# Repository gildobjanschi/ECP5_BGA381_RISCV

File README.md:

# Blue Whale Hardware
ECP5 FPGA board for developing a RISCV processor.

## Software
The ECP5 FPGA board was developed to enable the development of a RISCV processor and allow for for an extension connector. See the [RISCV_PROCESSOR](https://github.com/gildobjanschi/RISCV_PROCESSOR) project for detailed explanation of the Verilog code developed for this board.

## Project Status
The HW has been fully verified as part of the [RISCV_PROCESSOR](https://github.com/gildobjanschi/RISCV_PROCESSOR) project. An [extension board](https://github.com/gildobjanschi/ECP5_BGA381_RISCV_EXT)  was developed to test the extension interface. 

## How To setup KiCAD
Checkout the KiCAD project and open it. In the Configure Paths dialog add: Name: ECP5_BGA381_RISCV and Path: "The full path to the GitHub directory"/GitHub/ECP5_BGA381_RISCV

In the Manage Symbol Libraries click the Project Specific Libraries tab and add: Name: ECP5_BGA381_RISCV and Library Path: ${ECP5_BGA381_RISCV}/symbols/Symbols.kicad_sym

In the Manage Footprint Libraries click the Project Specific Libraries tab and add: Name: ECP5_BGA381_RISCV and Library Path: ${ECP5_BGA381_RISCV}/footprints/Footprints.pretty

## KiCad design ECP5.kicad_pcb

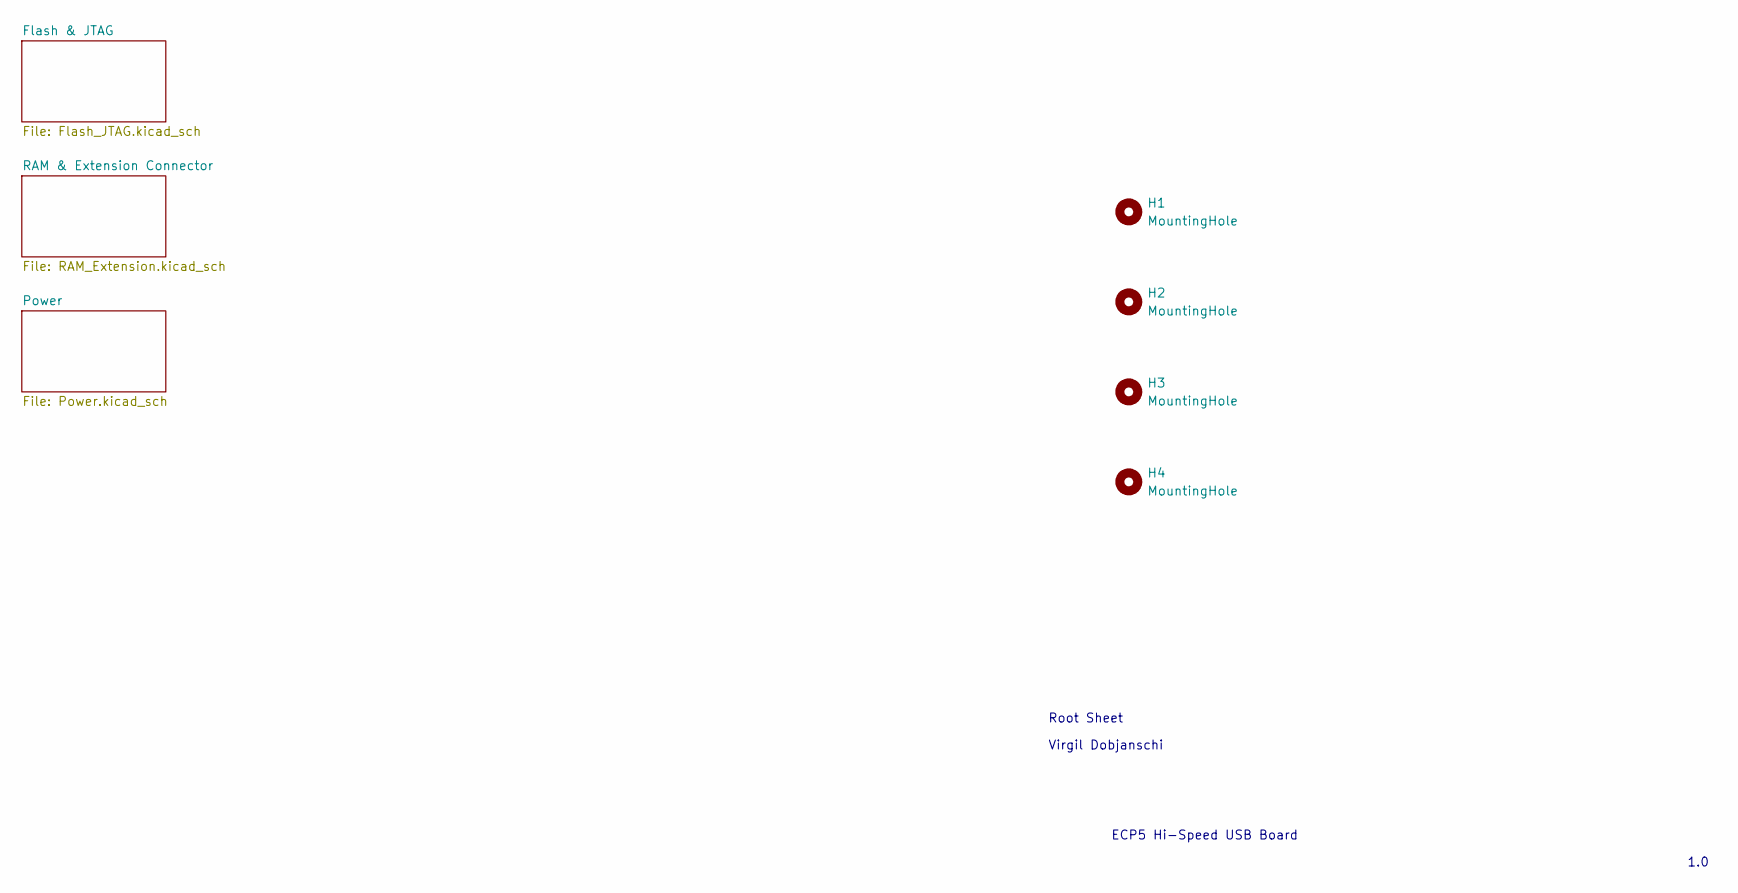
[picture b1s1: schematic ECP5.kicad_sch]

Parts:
H1, H2, H3, H4: MountingHole; MountingHole_3.2mm_M3

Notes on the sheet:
ECP5 Hi-Speed USB Board
Root Sheet
Virgil Dobjanschi
1.0

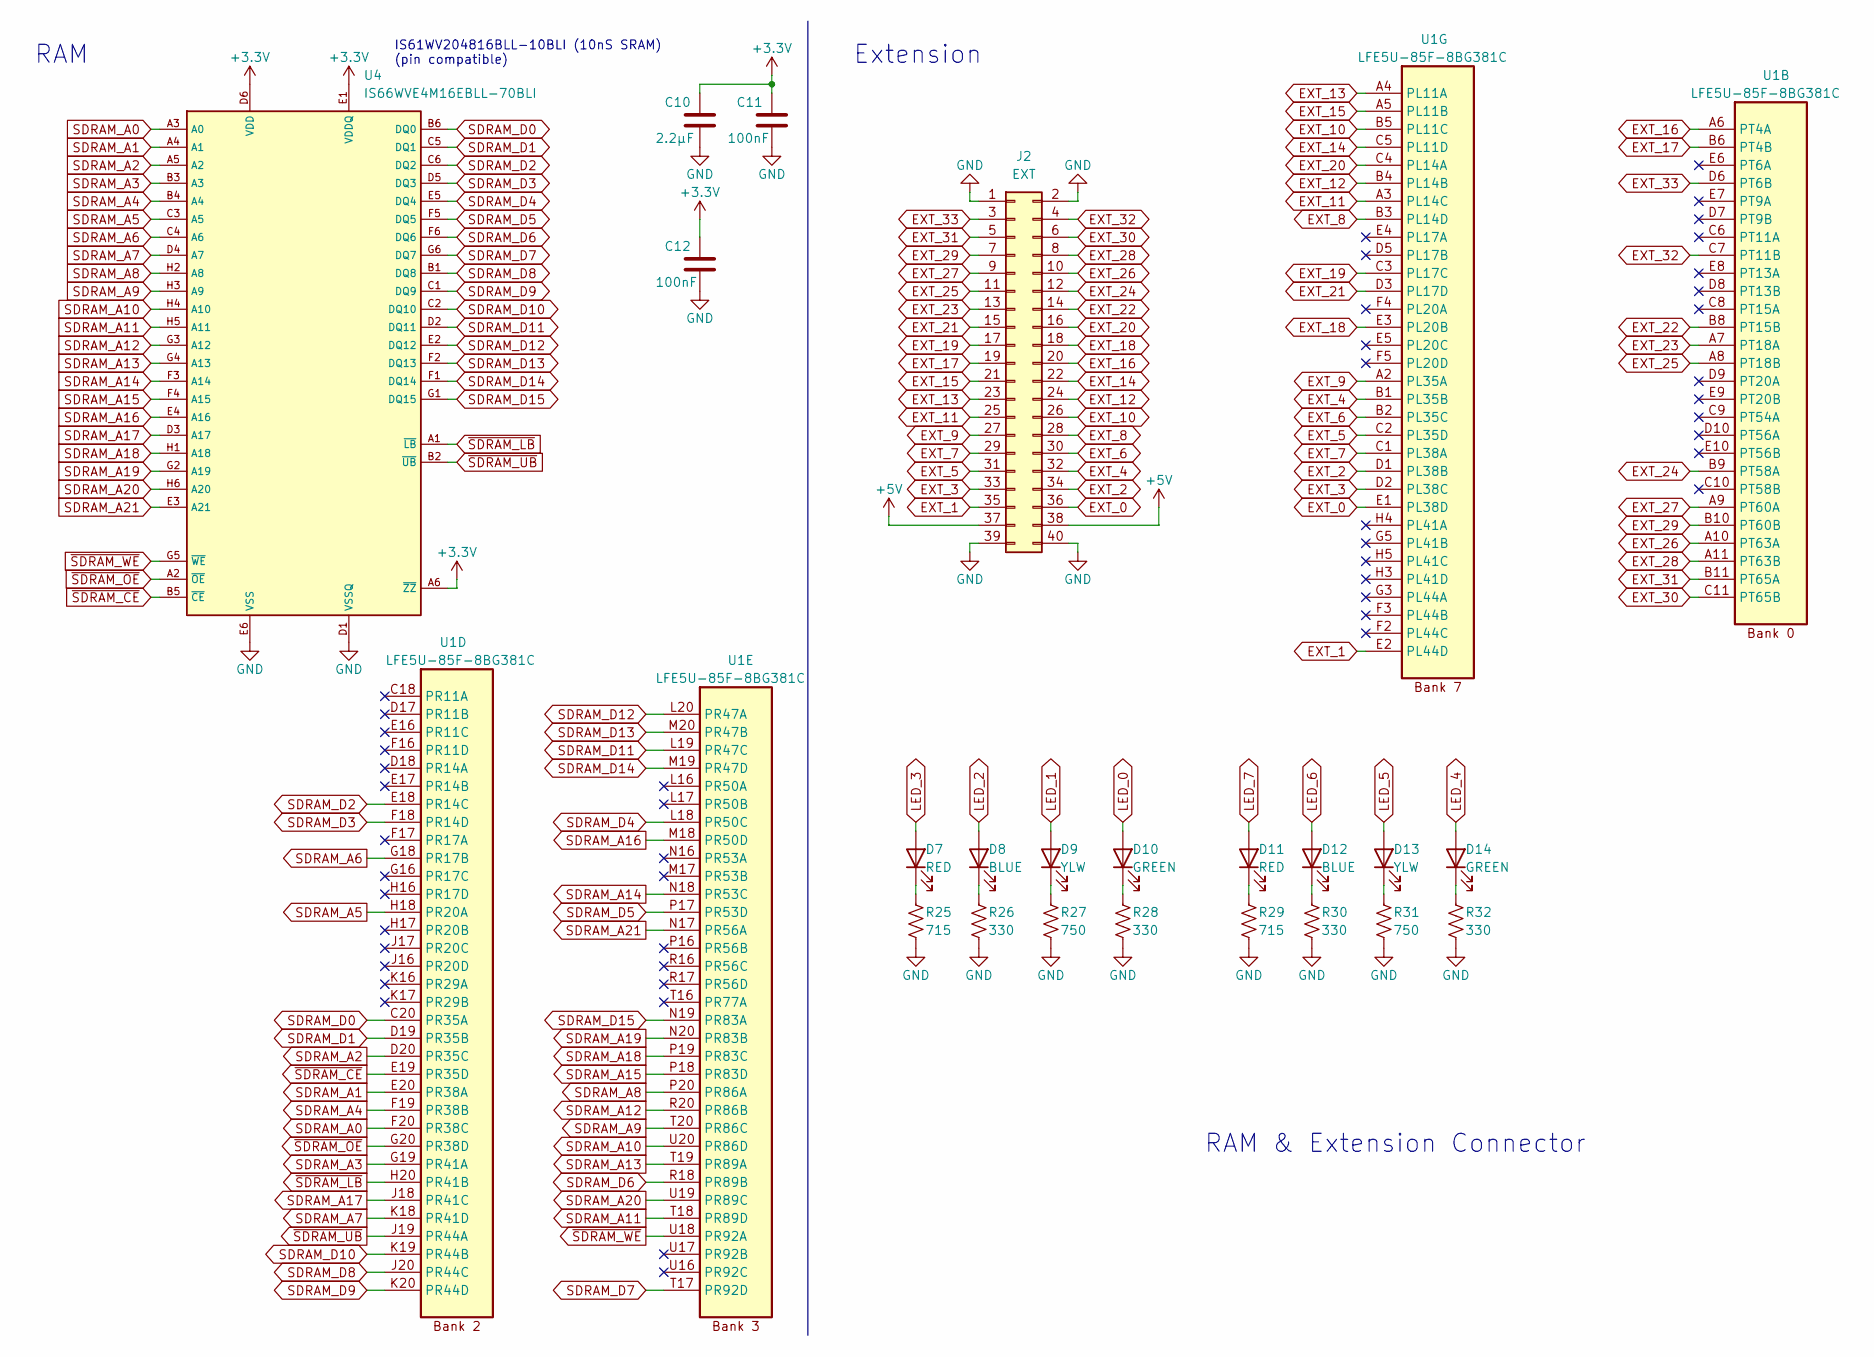
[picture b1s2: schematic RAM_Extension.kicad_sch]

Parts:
C10: 2.2µF; C_0603_1608Metric; MPN CL10B225KP8NNNC
C11, C12: 100nF; C_0603_1608Metric; MPN CL10B104KB8NNWC
D7, D11: RED; LED_0603_1608Metric; MPN APTD1608LSURCK
D8, D12: BLUE; LED_0603_1608Metric; MPN APTD1608LVBC/D
D9, D13: YLW; LED_0603_1608Metric; MPN APTD1608LSYCK/J3-PF
D10, D14: GREEN; LED_0603_1608Metric; MPN APTD1608LZGCK
J2: EXT; FTS-120-02-L-DV; MPN FTS-120-02-L-DV
R25, R29: 715; R_0603_1608Metric; MPN ERJ-3EKF7150V
R26, R28, R30, R32: 330; R_0603_1608Metric; MPN ERJ-3EKF3300V
R27, R31: 750; R_0603_1608Metric; MPN ERJ-3EKF7500V
U1: LFE5U-85F-8BG381C; BGA-381_pitch0.8mm_dia0.4mm; MPN LFE5U-85F-8BG381C
U4: IS66WVE4M16EBLL-70BLI; BGA48C75P8X6_800X600X120N; MPN IS66WVE4M16EBLL-70BLI

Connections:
+3.3V: C10.1, C11.1, C12.1, U4.A6 (~ZZ), U4.D6 (VDD), U4.E1 (VDDQ); also elsewhere on the board
+5V: J2.37, J2.38; also elsewhere on the board
EXT_0: J2.36, U1.E1 (PL38D)
EXT_1: J2.35, U1.E2 (PL44D)
EXT_2: J2.34, U1.D1 (PL38B)
EXT_3: J2.33, U1.D2 (PL38C)
EXT_4: J2.32, U1.B1 (PL35B)
EXT_5: J2.31, U1.C2 (PL35D)
EXT_6: J2.30, U1.B2 (PL35C)
EXT_7: J2.29, U1.C1 (PL38A)
EXT_8: J2.28, U1.B3 (PL14D)
EXT_9: J2.27, U1.A2 (PL35A)
EXT_10: J2.26, U1.B5 (PL11C)
EXT_11: J2.25, U1.A3 (PL14C)
EXT_12: J2.24, U1.B4 (PL14B)
EXT_13: J2.23, U1.A4 (PL11A)
EXT_14: J2.22, U1.C5 (PL11D)
EXT_15: J2.21, U1.A5 (PL11B)
EXT_16: J2.20, U1.A6 (PT4A)
EXT_17: J2.19, U1.B6 (PT4B)
EXT_18: J2.18, U1.E3 (PL20B)
EXT_19: J2.17, U1.C3 (PL17C)
EXT_20: J2.16, U1.C4 (PL14A)
EXT_21: J2.15, U1.D3 (PL17D)
EXT_22: J2.14, U1.B8 (PT15B)
EXT_23: J2.13, U1.A7 (PT18A)
EXT_24: J2.12, U1.B9 (PT58A)
EXT_25: J2.11, U1.A8 (PT18B)
EXT_26: J2.10, U1.A10 (PT63A)
EXT_27: J2.9, U1.A9 (PT60A)
EXT_28: J2.8, U1.A11 (PT63B)
EXT_29: J2.7, U1.B10 (PT60B)
EXT_30: J2.6, U1.C11 (PT65B)
EXT_31: J2.5, U1.B11 (PT65A)
EXT_32: J2.4, U1.C7 (PT11B)
EXT_33: J2.3, U1.D6 (PT6B)
GND: C10.2, C11.2, C12.2, J2.1, J2.2, J2.39, J2.40, R25.2, R26.2, R27.2, R28.2, R29.2, R30.2, R31.2, R32.2, U4.D1 (VSSQ), U4.E6 (VSS); also elsewhere on the board
LED_0: D10.2 (A); also elsewhere on the board
LED_1: D9.2 (A); also elsewhere on the board
LED_2: D8.2 (A); also elsewhere on the board
LED_3: D7.2 (A); also elsewhere on the board
LED_4: D14.2 (A); also elsewhere on the board
LED_5: D13.2 (A); also elsewhere on the board
LED_6: D12.2 (A); also elsewhere on the board
LED_7: D11.2 (A); also elsewhere on the board
unnamed: D7.1 (K), R25.1
unnamed: D8.1 (K), R26.1
unnamed: D9.1 (K), R27.1
unnamed: D10.1 (K), R28.1
unnamed: D11.1 (K), R29.1
unnamed: D12.1 (K), R30.1
unnamed: D13.1 (K), R31.1
unnamed: D14.1 (K), R32.1
SDRAM_A0: U1.F20 (PR38C), U4.A3 (A0)
SDRAM_A1: U1.E20 (PR38A), U4.A4 (A1)
SDRAM_A2: U1.D20 (PR35C), U4.A5 (A2)
SDRAM_A3: U1.G19 (PR41A), U4.B3 (A3)
SDRAM_A4: U1.F19 (PR38B), U4.B4 (A4)
SDRAM_A5: U1.H18 (PR20A), U4.C3 (A5)
SDRAM_A6: U1.G18 (PR17B), U4.C4 (A6)
SDRAM_A7: U1.K18 (PR41D), U4.D4 (A7)
SDRAM_A8: U1.P20 (PR86A), U4.H2 (A8)
SDRAM_A9: U1.T20 (PR86C), U4.H3 (A9)
SDRAM_A10: U1.U20 (PR86D), U4.H4 (A10)
SDRAM_A11: U1.T18 (PR89D), U4.H5 (A11)
SDRAM_A12: U1.R20 (PR86B), U4.G3 (A12)
SDRAM_A13: U1.T19 (PR89A), U4.G4 (A13)
SDRAM_A14: U1.N18 (PR53C), U4.F3 (A14)
SDRAM_A15: U1.P18 (PR83D), U4.F4 (A15)
SDRAM_A16: U1.M18 (PR50D), U4.E4 (A16)
SDRAM_A17: U1.J18 (PR41C), U4.D3 (A17)
SDRAM_A18: U1.P19 (PR83C), U4.H1 (A18)
SDRAM_A19: U1.N20 (PR83B), U4.G2 (A19)
SDRAM_A20: U1.U19 (PR89C), U4.H6 (A20)
SDRAM_A21: U1.N17 (PR56A), U4.E3 (A21)
SDRAM_D0: U1.C20 (PR35A), U4.B6 (DQ0)
SDRAM_D1: U1.D19 (PR35B), U4.C5 (DQ1)
SDRAM_D2: U1.E18 (PR14C), U4.C6 (DQ2)
SDRAM_D3: U1.F18 (PR14D), U4.D5 (DQ3)
SDRAM_D4: U1.L18 (PR50C), U4.E5 (DQ4)
SDRAM_D5: U1.P17 (PR53D), U4.F5 (DQ5)
SDRAM_D6: U1.R18 (PR89B), U4.F6 (DQ6)
SDRAM_D7: U1.T17 (PR92D), U4.G6 (DQ7)
SDRAM_D8: U1.J20 (PR44C), U4.B1 (DQ8)
SDRAM_D9: U1.K20 (PR44D), U4.C1 (DQ9)
SDRAM_D10: U1.K19 (PR44B), U4.C2 (DQ10)
SDRAM_D11: U1.L19 (PR47C), U4.D2 (DQ11)
SDRAM_D12: U1.L20 (PR47A), U4.E2 (DQ12)
SDRAM_D13: U1.M20 (PR47B), U4.F2 (DQ13)
SDRAM_D14: U1.M19 (PR47D), U4.F1 (DQ14)
SDRAM_D15: U1.N19 (PR83A), U4.G1 (DQ15)
~SDRAM_CE: U1.E19 (PR35D), U4.B5 (~CE)
~SDRAM_LB: U1.H20 (PR41B), U4.A1 (~LB)
~SDRAM_OE: U1.G20 (PR38D), U4.A2 (~OE)
~SDRAM_UB: U1.J19 (PR44A), U4.B2 (~UB)
~SDRAM_WE: U1.U18 (PR92A), U4.G5 (~WE)

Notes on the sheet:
RAM
Extension
IS61WV204816BLL-10BLI (10nS SRAM) (pin compatible)
RAM & Extension Connector

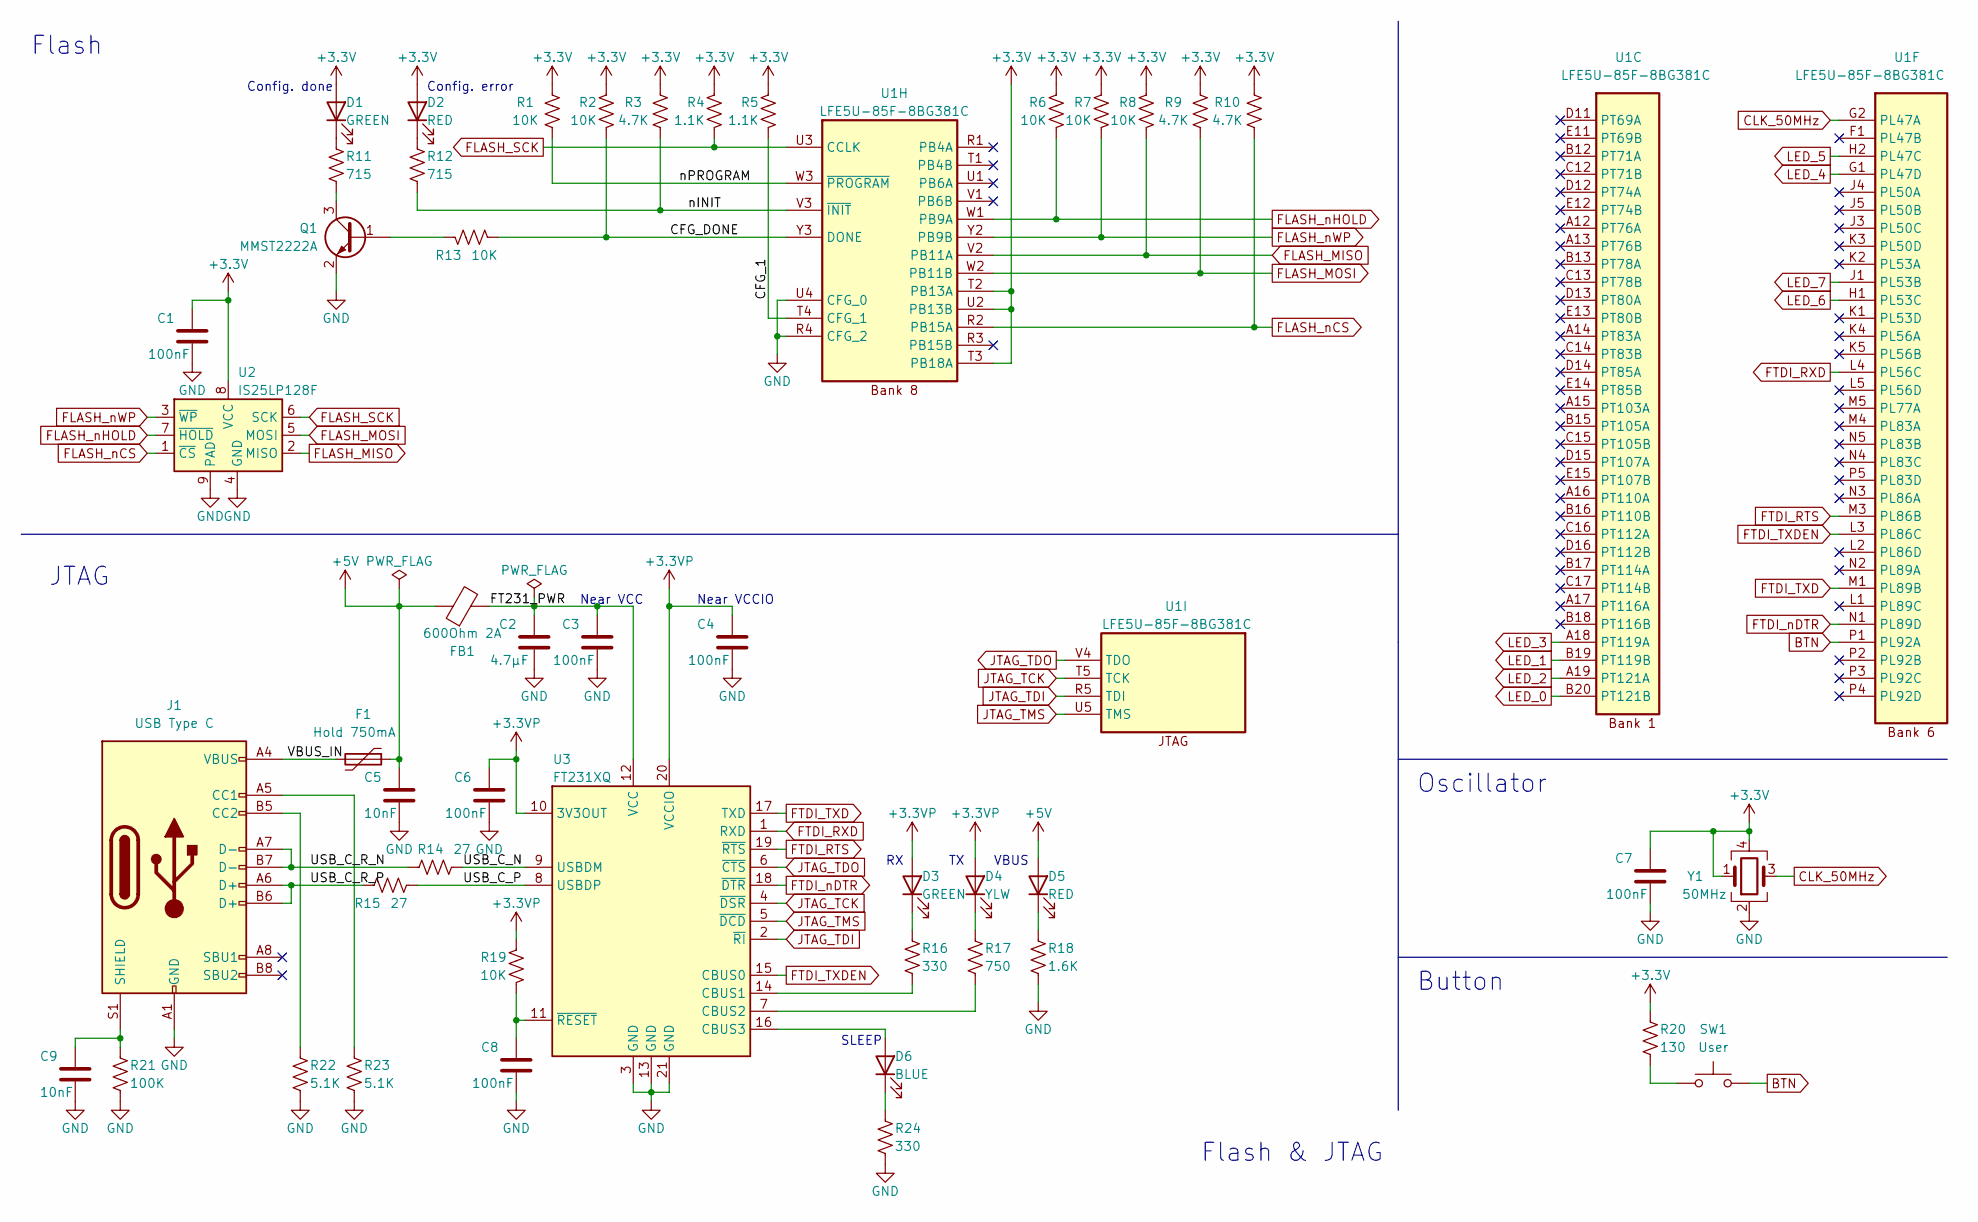
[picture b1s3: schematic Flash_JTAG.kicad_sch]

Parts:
C1, C3, C4, C6, C7, C8: 100nF; C_0603_1608Metric; MPN CL10B104KB8NNWC
C2: 4.7µF; C_0603_1608Metric; MPN CL10A475KP8NNNC
C5, C9: 10nF; C_0603_1608Metric; MPN CL10B103KB8NNWC
D1, D3: GREEN; LED_0603_1608Metric; MPN APTD1608LZGCK
D2, D5: RED; LED_0603_1608Metric; MPN APTD1608LSURCK
D4: YLW; LED_0603_1608Metric; MPN APTD1608LSYCK/J3-PF
D6: BLUE; LED_0603_1608Metric; MPN APTD1608LVBC/D
F1: Hold 750mA; Fuse_1812_4532Metric; MPN 0ZCG0075FF2C
FB1: 600Ohm 2A; L_0805_2012Metric; MPN 78279220601
J1: USB Type C; USB_C_Receptacle_GCT_USB4105-xx-A_16P_TopMnt_Horizontal; MPN USB4105-GF-A-120
Q1: MMST2222A; SOT-323_SC-70; MPN MMST2222A-7-F
R1, R2, R6, R7, R8, R13, R19: 10K; R_0603_1608Metric; MPN ERJ-3EKF1002V
R3, R9, R10: 4.7K; R_0603_1608Metric; MPN ERJ-3EKF4701V
R4, R5: 1.1K; R_0603_1608Metric; MPN ERJ-3EKF1101V
R11, R12: 715; R_0603_1608Metric; MPN ERJ-3EKF7150V
R14, R15: 27; R_0603_1608Metric; MPN ERJ-3EKF27R0V
R16, R24: 330; R_0603_1608Metric; MPN ERJ-3EKF3300V
R17: 750; R_0603_1608Metric; MPN ERJ-3EKF7500V
R18: 1.6K; R_0603_1608Metric; MPN ERJ-3EKF1601V
R20: 130; R_0603_1608Metric; MPN ERJ-3EKF1300V
R21: 100K; R_0603_1608Metric; MPN ERJ-3EKF1003V
R22, R23: 5.1K; R_0603_1608Metric; MPN ERJ-3EKF5101V
SW1: User; SW_SPST_PTS645; MPN PTS645SK43SMTR92 LFS
U1: LFE5U-85F-8BG381C; BGA-381_pitch0.8mm_dia0.4mm; MPN LFE5U-85F-8BG381C
U2: IS25LP128F; WSON-8-1EP_6x5mm_P1.27mm_EP3.4x4.3mm; MPN IS25LP128-JKLE
U3: FT231XQ; QFN-20-1EP_4x4mm_P0.5mm_EP2.5x2.5mm; MPN FT231XQ-R
Y1: 50MHz; Oscillator_SMD_Diodes_FN-4Pin_7.0x5.0mm; MPN ECS-7050MV-500-DM-TR

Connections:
+3.3V: C1.1, C7.1, D1.2 (A), D2.2 (A), R1.2, R2.1, R3.2, R4.1, R5.1, R6.1, R7.1, R8.1, R9.2, R10.2, R20.1, U1.T2 (PB13A), U1.T3 (PB18A), U1.U2 (PB13B), U2.8 (VCC), Y1.1, Y1.4; also elsewhere on the board
+3.3VP: C4.1, C6.1, D3.2 (A), D4.2 (A), R19.1, U3.10 (3V3OUT), U3.20 (VCCIO)
+5V: C5.1, D5.2 (A), F1.1, FB1.1; also elsewhere on the board
/Flash & JTAG/CFG_1: R5.2, U1.T4 (CFG_1)
/Flash & JTAG/CFG_DONE: R2.2, R13.2, U1.Y3 (DONE)
/Flash & JTAG/FT231_PWR: C2.1, C3.1, FB1.2, U3.12 (VCC)
/Flash & JTAG/USB_C_N: R14.2, U3.9 (USBDM)
/Flash & JTAG/USB_C_P: R15.2, U3.8 (USBDP)
/Flash & JTAG/USB_C_R_N: J1.A7 (D-), J1.B7 (D-), R14.1
/Flash & JTAG/USB_C_R_P: J1.A6 (D+), J1.B6 (D+), R15.1
/Flash & JTAG/VBUS_IN: F1.2, J1.A4 (VBUS), J1.A9 (VBUS), J1.B4 (VBUS), J1.B9 (VBUS)
/Flash & JTAG/nINIT: R3.1, R12.2, U1.V3 (~INIT)
/Flash & JTAG/nPROGRAM: R1.1, U1.W3 (~PROGRAM)
BTN: SW1.2, U1.P1 (PL92A)
CLK_50MHz: U1.G2 (PL47A), Y1.3
FLASH_MISO: R8.2, U1.V2 (PB11A), U2.2 (MISO)
FLASH_MOSI: R9.1, U1.W2 (PB11B), U2.5 (MOSI)
FLASH_SCK: R4.2, U1.U3 (CCLK), U2.6 (SCK)
FLASH_nCS: R10.1, U1.R2 (PB15A), U2.1 (~CS)
FLASH_nHOLD: R6.2, U1.W1 (PB9A), U2.7 (~HOLD)
FLASH_nWP: R7.2, U1.Y2 (PB9B), U2.3 (~WP)
FTDI_RTS: U1.M3 (PL86B), U3.19 (~RTS)
FTDI_RXD: U1.L4 (PL56C), U3.1 (RXD)
FTDI_TXD: U1.M1 (PL89B), U3.17 (TXD)
FTDI_TXDEN: U1.L3 (PL86C), U3.15 (CBUS0)
FTDI_nDTR: U1.N1 (PL89D), U3.18 (~DTR)
GND: C1.2, C2.2, C3.2, C4.2, C5.2, C6.2, C7.2, C8.2, C9.2, J1.A1 (GND), J1.A12 (GND), J1.B1 (GND), J1.B12 (GND), Q1.2 (E), R18.2, R21.2, R22.2, R23.2, R24.2, U1.R4 (CFG_2), U1.U4 (CFG_0), U2.4 (GND), U2.9 (PAD), U3.3 (GND), U3.13 (GND), U3.21 (GND), Y1.2; also elsewhere on the board
JTAG_TCK: U1.T5 (TCK), U3.4 (~DSR)
JTAG_TDI: U1.R5 (TDI), U3.2 (~RI)
JTAG_TDO: U1.V4 (TDO), U3.6 (~CTS)
JTAG_TMS: U1.U5 (TMS), U3.5 (~DCD)
LED_0: U1.B20 (PT121B); also elsewhere on the board
LED_1: U1.B19 (PT119B); also elsewhere on the board
LED_2: U1.A19 (PT121A); also elsewhere on the board
LED_3: U1.A18 (PT119A); also elsewhere on the board
LED_4: U1.G1 (PL47D); also elsewhere on the board
LED_5: U1.H2 (PL47C); also elsewhere on the board
LED_6: U1.H1 (PL53C); also elsewhere on the board
LED_7: U1.J1 (PL53B); also elsewhere on the board
unnamed: D1.1 (K), R11.1
unnamed: D2.1 (K), R12.1
unnamed: D3.1 (K), R16.1
unnamed: D4.1 (K), R17.1
unnamed: D5.1 (K), R18.1
unnamed: D6.2 (A), U3.16 (CBUS3)
unnamed: D6.1 (K), R24.1
unnamed: J1.A5 (CC1), R23.1
unnamed: J1.B5 (CC2), R22.1
unnamed: C9.1, J1.S1 (SHIELD), R21.1
unnamed: Q1.1 (B), R13.1
unnamed: Q1.3 (C), R11.2
unnamed: R20.2, SW1.1
unnamed: R16.2, U3.14 (CBUS1)
unnamed: R17.2, U3.7 (CBUS2)
unnamed: C8.1, R19.2, U3.11 (~RESET)

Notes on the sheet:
Near VCCIO
Flash
Near VCC
Flash & JTAG
SLEEP
Oscillator
Button
VBUS
Config. done
JTAG
Config. error

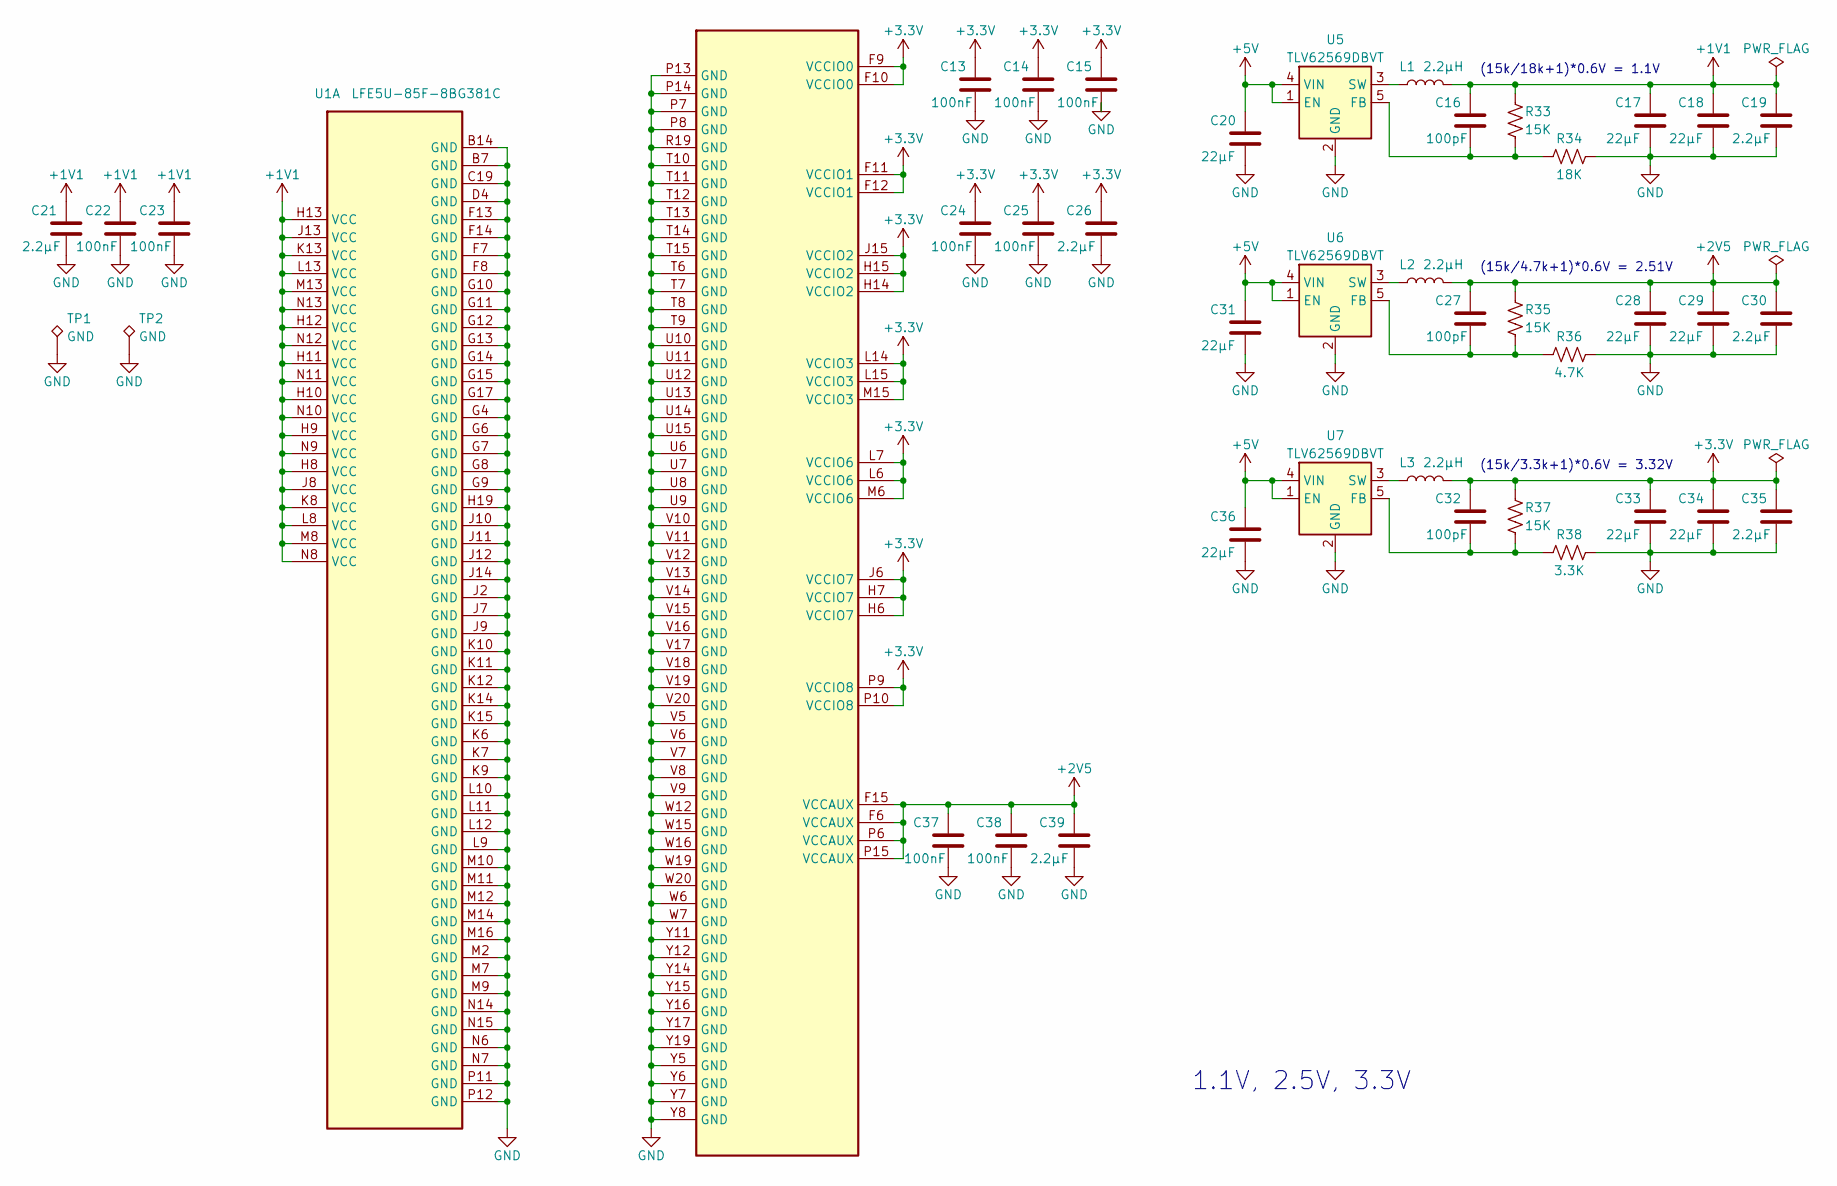
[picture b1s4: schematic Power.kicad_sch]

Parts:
C13, C14, C15, C22, C23, C24, C25, C37, C38: 100nF; C_0603_1608Metric; MPN CL10B104KB8NNWC
C16, C27, C32: 100pF; C_0603_1608Metric; MPN CL10C101FB81PNC
C17, C18, C20, C28, C29, C31, C33, C34, C36: 22µF; C_0603_1608Metric; MPN CL10A226MP8NUNE
C19, C21, C26, C30, C35, C39: 2.2µF; C_0603_1608Metric; MPN CL10B225KP8NNNC
L1, L2, L3: 2.2µH; L_1210_3225Metric; MPN DFE322512F-2R2M=P2
R33, R35, R37: 15K; R_0603_1608Metric; MPN ERJ-3EKF1502V
R34: 18K; R_0603_1608Metric; MPN ERJ-3EKF1802V
R36: 4.7K; R_0603_1608Metric; MPN ERJ-3EKF4701V
R38: 3.3K; R_0603_1608Metric; MPN ERJ-3EKF3301V
TP1, TP2: GND; TestPoint_THTPad_D2.0mm_Drill1.0mm; MPN 5001
U1: LFE5U-85F-8BG381C; BGA-381_pitch0.8mm_dia0.4mm; MPN LFE5U-85F-8BG381C
U5, U6, U7: TLV62569DBVT; SOT-23-5; MPN TLV62569DBVT

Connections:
+1V1: C16.1, C17.1, C18.1, C19.1, C21.1, C22.1, C23.1, L1.2, R33.1, U1.H8 (VCC), U1.H9 (VCC), U1.H10 (VCC), U1.H11 (VCC), U1.H12 (VCC), U1.H13 (VCC), U1.J8 (VCC), U1.J13 (VCC), U1.K8 (VCC), U1.K13 (VCC), U1.L8 (VCC), U1.L13 (VCC), U1.M8 (VCC), U1.M13 (VCC), U1.N8 (VCC), U1.N9 (VCC), U1.N10 (VCC), U1.N11 (VCC), U1.N12 (VCC), U1.N13 (VCC)
+2V5: C27.1, C28.1, C29.1, C30.1, C37.1, C38.1, C39.1, L2.2, R35.1, U1.F6 (VCCAUX), U1.F15 (VCCAUX), U1.P6 (VCCAUX), U1.P15 (VCCAUX)
+3.3V: C13.1, C14.1, C15.1, C24.1, C25.1, C26.1, C32.1, C33.1, C34.1, C35.1, L3.2, R37.1, U1.F9 (VCCIO0), U1.F10 (VCCIO0), U1.F11 (VCCIO1), U1.F12 (VCCIO1), U1.H6 (VCCIO7), U1.H7 (VCCIO7), U1.H14 (VCCIO2), U1.H15 (VCCIO2), U1.J6 (VCCIO7), U1.J15 (VCCIO2), U1.L6 (VCCIO6), U1.L7 (VCCIO6), U1.L14 (VCCIO3), U1.L15 (VCCIO3), U1.M6 (VCCIO6), U1.M15 (VCCIO3), U1.P9 (VCCIO8), U1.P10 (VCCIO8); also elsewhere on the board
+5V: C20.1, C31.1, C36.1, U5.1 (EN), U5.4 (VIN), U6.1 (EN), U6.4 (VIN), U7.1 (EN), U7.4 (VIN); also elsewhere on the board
GND: C13.2, C14.2, C15.2, C17.2, C18.2, C19.2, C20.2, C21.2, C22.2, C23.2, C24.2, C25.2, C26.2, C28.2, C29.2, C30.2, C31.2, C33.2, C34.2, C35.2, C36.2, C37.2, C38.2, C39.2, R34.2, R36.2, R38.2, TP1.1, TP2.1, U1.B7 (GND), U1.B14 (GND), U1.C19 (GND), U1.D4 (GND), U1.F7 (GND), U1.F8 (GND), U1.F13 (GND), U1.F14 (GND), U1.G4 (GND), U1.G6 (GND), U1.G7 (GND), U1.G8 (GND), U1.G9 (GND), U1.G10 (GND), U1.G11 (GND), U1.G12 (GND), U1.G13 (GND), U1.G14 (GND), U1.G15 (GND), U1.G17 (GND), U1.H19 (GND), U1.J2 (GND), U1.J7 (GND), U1.J9 (GND), U1.J10 (GND), U1.J11 (GND), U1.J12 (GND), U1.J14 (GND), U1.K6 (GND), U1.K7 (GND), U1.K9 (GND), U1.K10 (GND), U1.K11 (GND), U1.K12 (GND), U1.K14 (GND), U1.K15 (GND), U1.L9 (GND), U1.L10 (GND), U1.L11 (GND), U1.L12 (GND), U1.M2 (GND), U1.M7 (GND), U1.M9 (GND), U1.M10 (GND), U1.M11 (GND), U1.M12 (GND), U1.M14 (GND), U1.M16 (GND), U1.N6 (GND), U1.N7 (GND), U1.N14 (GND), U1.N15 (GND), U1.P7 (GND), U1.P8 (GND), U1.P11 (GND), U1.P12 (GND), U1.P13 (GND), U1.P14 (GND), U1.R19 (GND), U1.T6 (GND), U1.T7 (GND), U1.T8 (GND), U1.T9 (GND), U1.T10 (GND), U1.T11 (GND), U1.T12 (GND), U1.T13 (GND), U1.T14 (GND), U1.T15 (GND), U1.U6 (GND), U1.U7 (GND), U1.U8 (GND), U1.U9 (GND), U1.U10 (GND), U1.U11 (GND), U1.U12 (GND), U1.U13 (GND), U1.U14 (GND), U1.U15 (GND), U1.V5 (GND), U1.V6 (GND), U1.V7 (GND), U1.V8 (GND), U1.V9 (GND), U1.V10 (GND), U1.V11 (GND), U1.V12 (GND), U1.V13 (GND), U1.V14 (GND), U1.V15 (GND), U1.V16 (GND), U1.V17 (GND), U1.V18 (GND), U1.V19 (GND), U1.V20 (GND), U1.W6 (GND), U1.W7 (GND), U1.W12 (GND), U1.W15 (GND), U1.W16 (GND), U1.W19 (GND), U1.W20 (GND), U1.Y5 (GND), U1.Y6 (GND), U1.Y7 (GND), U1.Y8 (GND), U1.Y11 (GND), U1.Y12 (GND), U1.Y14 (GND), U1.Y15 (GND), U1.Y16 (GND), U1.Y17 (GND), U1.Y19 (GND), U5.2 (GND), U6.2 (GND), U7.2 (GND); also elsewhere on the board
unnamed: C16.2, R33.2, R34.1, U5.5 (FB)
unnamed: L1.1, U5.3 (SW)
unnamed: C27.2, R35.2, R36.1, U6.5 (FB)
unnamed: L2.1, U6.3 (SW)
unnamed: C32.2, R37.2, R38.1, U7.5 (FB)
unnamed: L3.1, U7.3 (SW)

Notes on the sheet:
(15k/3.3k+1)*0.6V = 3.32V
(15k/18k+1)*0.6V = 1.1V
(15k/4.7k+1)*0.6V = 2.51V
1.1V, 2.5V, 3.3V

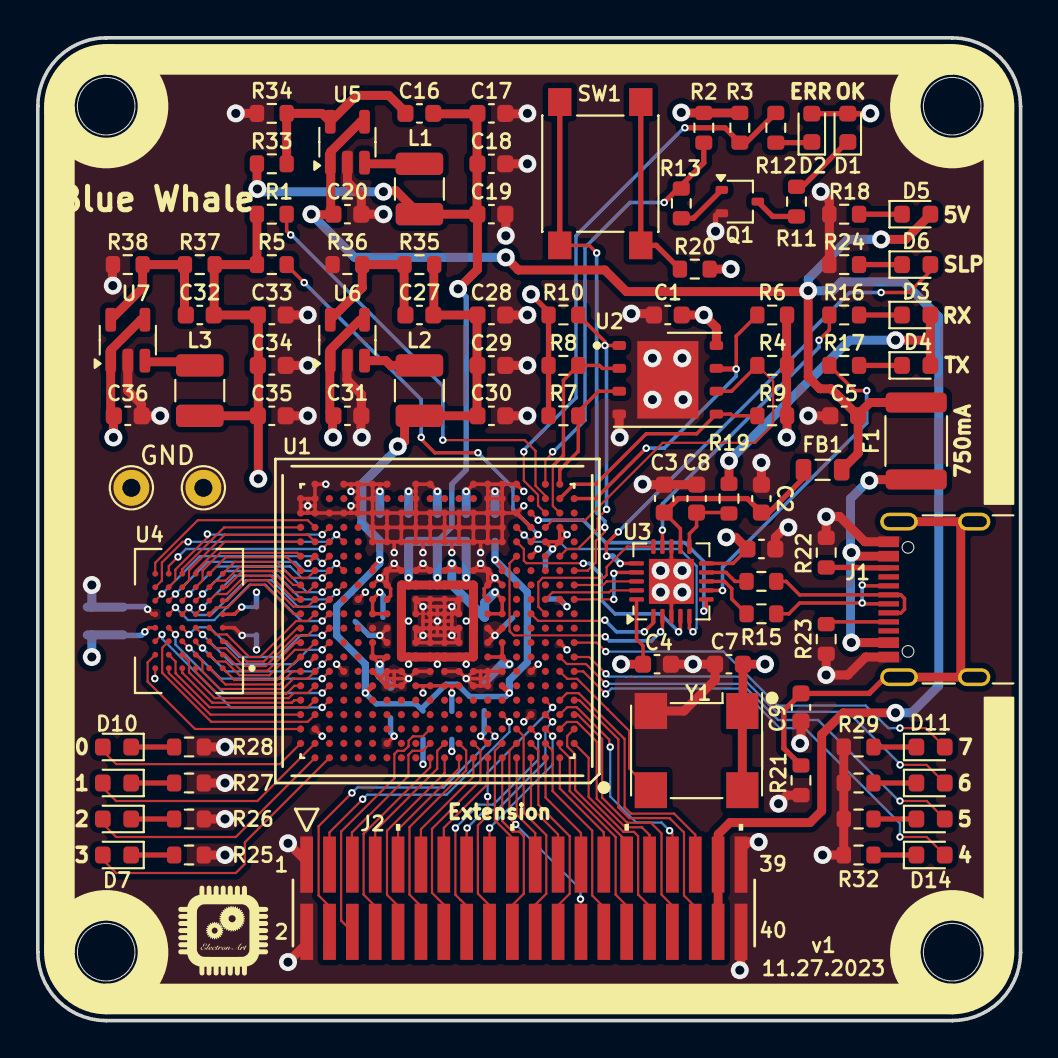
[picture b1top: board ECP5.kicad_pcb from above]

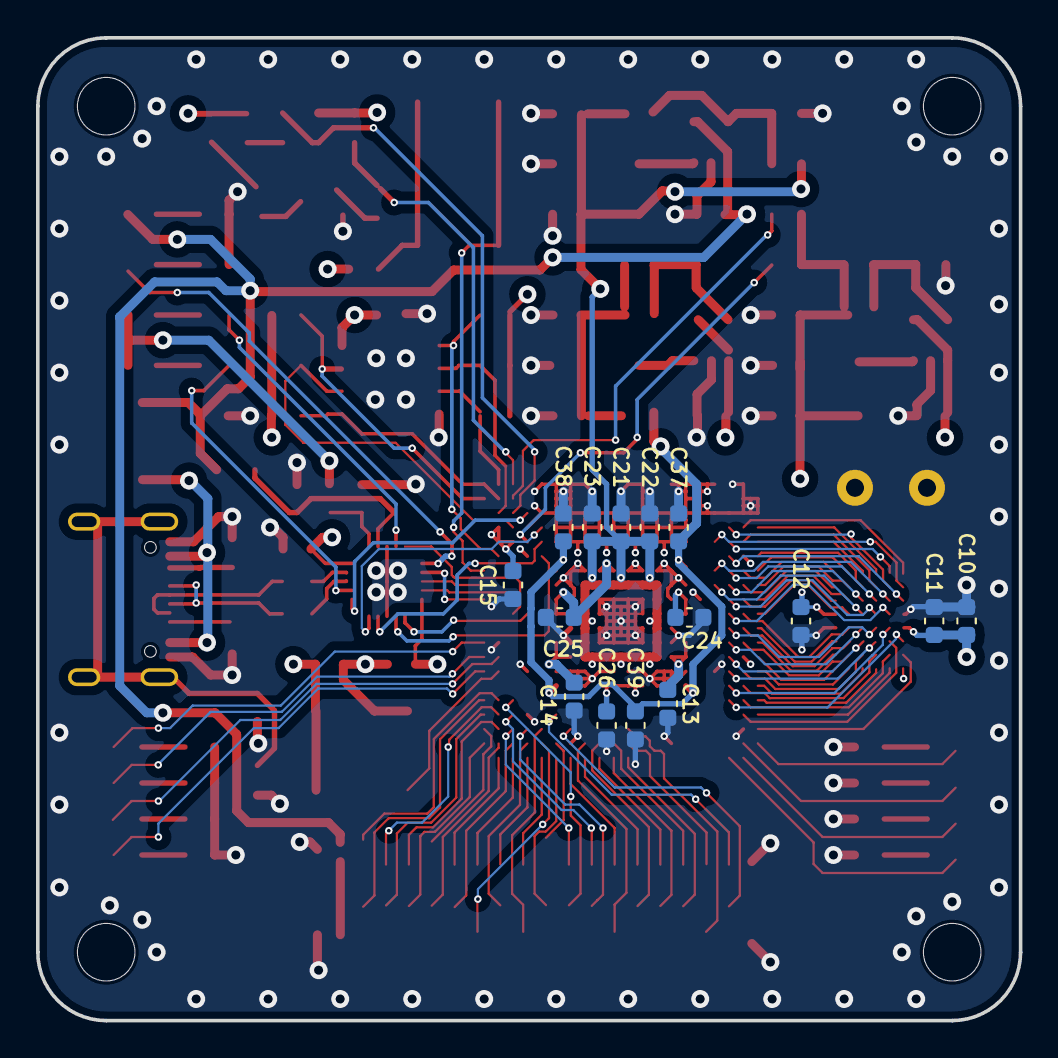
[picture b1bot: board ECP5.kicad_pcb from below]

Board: 4 copper layers, 54.6 x 54.6 mm, 114 parts (15 on the bottom side), 148 nets.

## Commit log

2024-01-15 FPGA first commit
    Added Kicad project file, schematics. PCB, symbols, footprints, 3dmodels.
2024-01-17 Update README.md
    Linked image to README.md
2024-07-06 Switched to project library
2024-09-06 Changed the name of the project path to ECP5_BGA381_RISCV
